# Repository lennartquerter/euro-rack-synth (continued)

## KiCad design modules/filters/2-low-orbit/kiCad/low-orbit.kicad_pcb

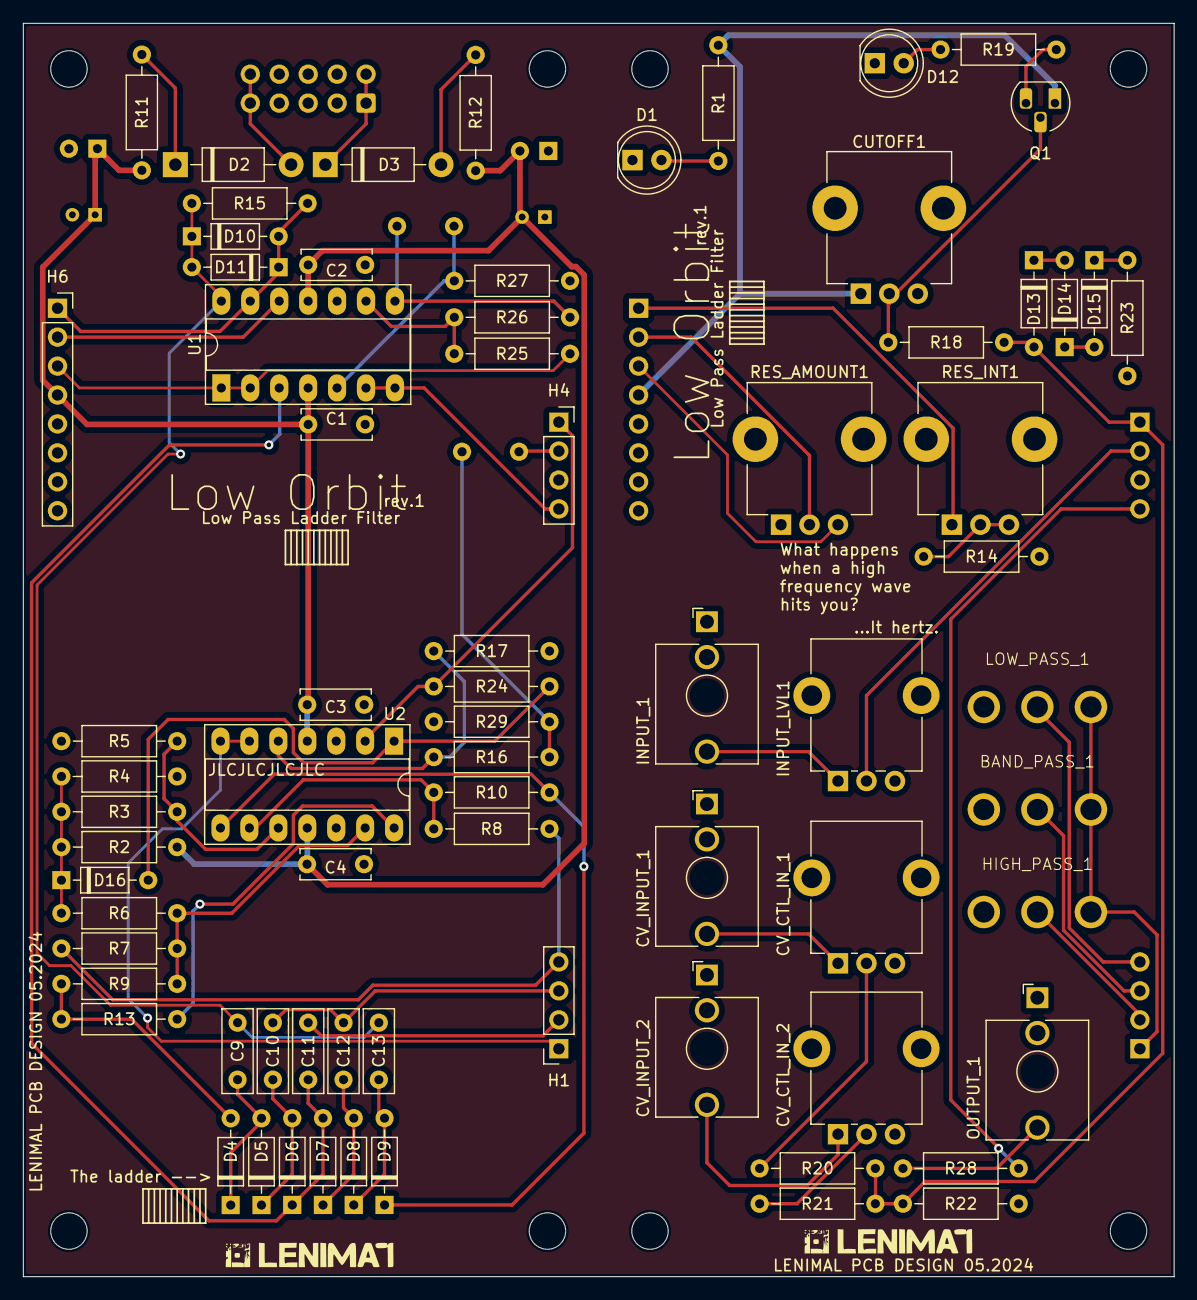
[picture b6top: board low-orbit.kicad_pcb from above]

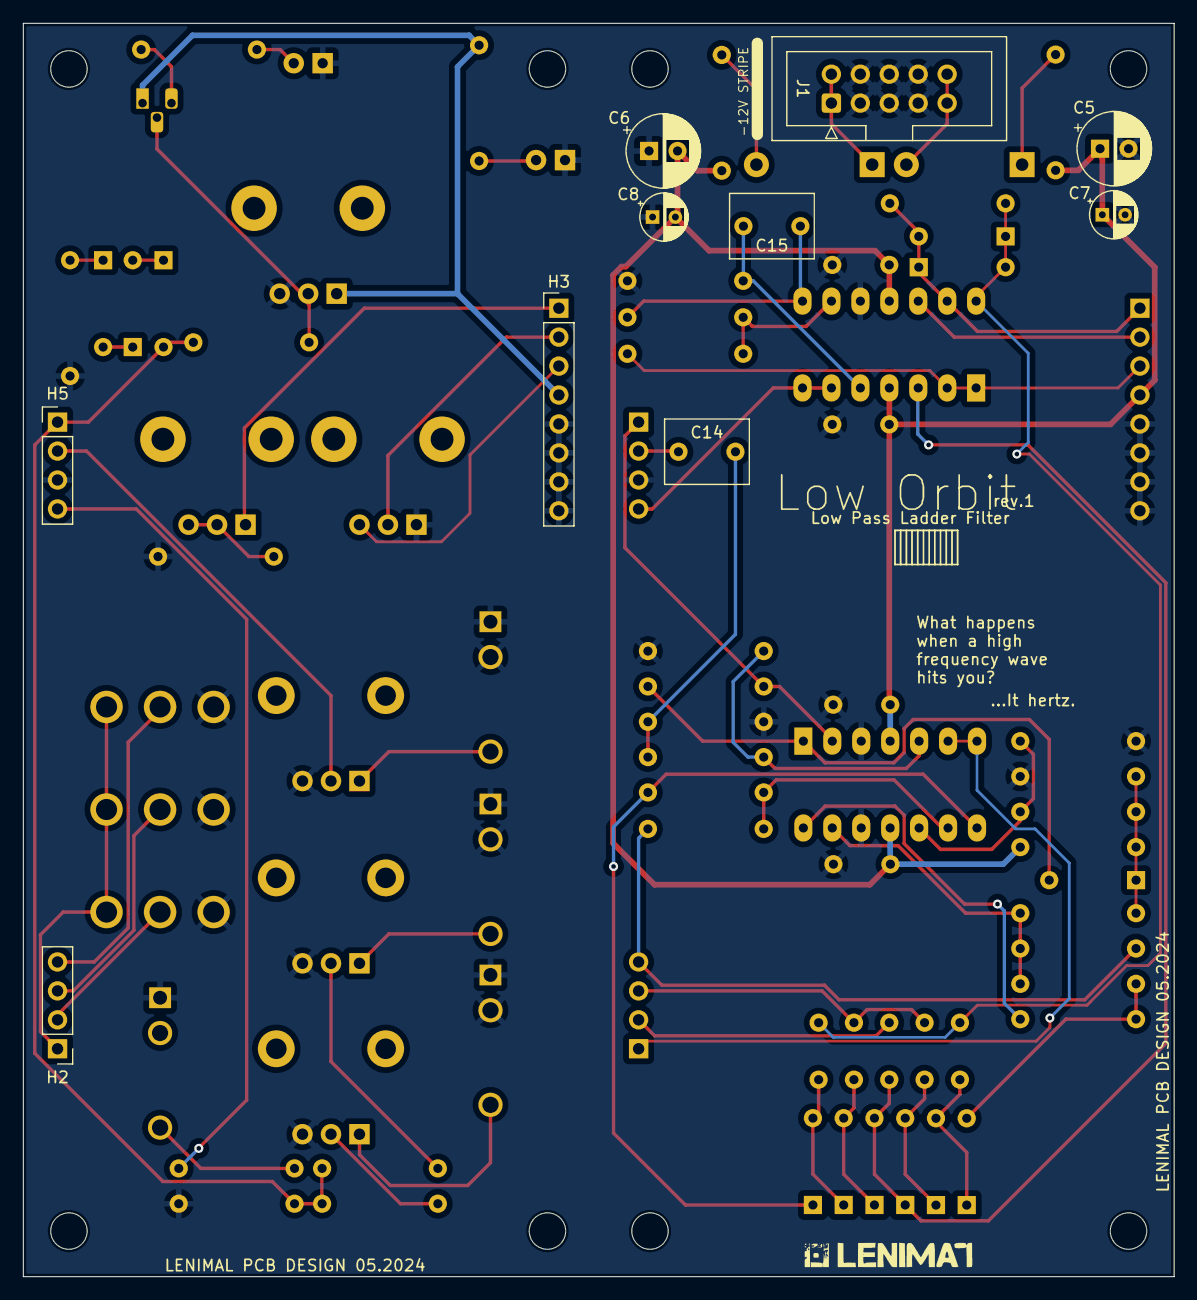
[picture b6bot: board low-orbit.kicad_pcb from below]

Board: 2 copper layers, 101.0 x 110.0 mm, 91 parts (10 on the bottom side), 60 nets.

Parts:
BAND_PASS_1: BAND_PASS; SW_default
C1, C2, C3, C4: 0.1uF; C_Disc_D6.0mm_W2.5mm_P5.00mm
C5, C6: 47uF; CP_Radial_D6.3mm_P2.50mm
C7, C8: 0.1uF; CP_Radial_D4.0mm_P2.00mm
C9, C10, C11, C12, C13: 1nF [2,5%]; C_RECT_WIMA_0.1uF
C14: 1uF; C_RECT_MKT_1uF
C15: C_1uF (MKS); C_RECT_MKT_1uF
CUTOFF1: B100K; Potentiometer_TT_P0915N
CV_CTL_IN_1, CV_CTL_IN_2: B100K; Potentiometer_Alpha_RD901F-40-00D_Single_Vertical_CircularH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
CV_INPUT_1: CV_INPUT_1; Jack_3.5mm_QingPu_WQP-PJ398SM_Vertical_CircularHoles
CV_INPUT_2: CV_INPUT_2; Jack_3.5mm_QingPu_WQP-PJ398SM_Vertical_CircularHoles
D1, D12: LED; LED_D5.0mm (center Aligned)
D2, D3: 1N5819; D_DO-41_SOD81_P10.16mm_Horizontal
D4, D5, D6, D7, D8, D9, D10, D11, D13, D14, D15, D16: 1N4148; D_DO-35_SOD27_P7.62mm_Horizontal
H1, H4: PinSocket_01x04; PinSocket_1x04_P2.54mm_Vertical
H2, H5: PinHeader_01x04; PinHeader_1x04_P2.54mm_Vertical
H3: PinHeader_01x08; PinHeader_1x08_P2.54mm_Vertical
H6: PinSocket_01x08; PinSocket_1x08_P2.54mm_Vertical
H7, H8, H9, H10, H11, H12, H13, H14: MountingHole; MountingHole_3.2mm_M3
HIGH_PASS_1: HIGH_PASS; SW_default
INPUT_1: IN; Jack_3.5mm_QingPu_WQP-PJ398SM_Vertical_CircularHoles
INPUT_LVL1: B100K; Potentiometer_Alpha_RD901F-40-00D_Single_Vertical_CircularH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
J1: PWR; IDC-Header_2x05_P2.54mm_Vertical
LOW_PASS_1: LOW_PASS; SW_default
OUTPUT_1: FILTER_OUT; Jack_3.5mm_QingPu_WQP-PJ398SM_Vertical_CircularHoles
Q1: BC548; TO-92_HandSolder
R1, R19: 470R; R_Default (DIN0207)
R2, R15, R18, R27, R29: 100K; R_Default (DIN0207)
R3, R5, R6, R7, R8, R9, R10: 33K [1%]; R_Default (DIN0207)
R4: 27K; R_Default (DIN0207)
R11, R12: 10R; R_Default (DIN0207)
R13: 2K; R_Default (DIN0207)
R14, R23, R25, R28: 1K; R_Default (DIN0207)
R16, R26: 33K; R_Default (DIN0207)
R17: 680R; R_Default (DIN0207)
R20, R21, R22: 47K [1%]; R_Default (DIN0207)
R24: 14K; R_Default (DIN0207)
RES_AMOUNT1: B100K; Potentiometer_TT_P0915N
RES_INT1: B50K; Potentiometer_TT_P0915N
U1, U2: TL074; DIP-14_W7.62mm_Socket_LongPads

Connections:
+12V: C1.1, C3.1, C5.1, C7.1, CUTOFF1.1, H3.4, H6.4, Q1.1 (C), R1.1, R11.1, U1.4 (V+), U2.4 (V+)
-12V: C2.2, C4.2, C6.2, C8.2, R2.2, R12.1, U1.11 (V-), U2.11 (V-)
/cv-input/cv_out: D16.1 (K), R2.1, R3.2, R4.2, R6.1
/input/output: H1.1, U2.6 (-), U2.7
/output/input: H6.3, R25.1, U1.1, U1.2 (-)
/resonance/input: H3.3, RES_AMOUNT1.3
/resonance/output: C9.1, C13.1, D10.1 (K), D11.2 (A), R15.1, U1.14
GNDREF: BAND_PASS_1.1 (A), C1.2, C2.1, C3.2, C4.1, C5.2, C6.1, C7.2, C8.1, CUTOFF1.3, CV_CTL_IN_1.3, CV_CTL_IN_2.3, CV_INPUT_1.S, CV_INPUT_1.TN, CV_INPUT_2.S, CV_INPUT_2.TN, D1.1 (K), D12.1 (K), H3.5, H3.6, H3.7, H3.8, H4.3, H5.3, H6.5, H6.6, H6.7, H6.8, HIGH_PASS_1.1 (A), INPUT_1.S, INPUT_1.TN, INPUT_LVL1.3, J1.3, J1.4, J1.5, J1.6, J1.7, J1.8, LOW_PASS_1.1 (A), OUTPUT_1.S, R4.1, R5.1, R14.2, R17.1, R22.2, R23.2, R27.1, R29.2, RES_AMOUNT1.1, U1.10 (+), U2.3 (+), U2.12 (+)
unnamed: BAND_PASS_1.2 (B), H2.3
unnamed: BAND_PASS_1.3 (C), H2.1, HIGH_PASS_1.3 (C), LOW_PASS_1.3 (C)
unnamed: C14.2, R16.2, R29.1
unnamed: C15.1, R26.2, U1.8
unnamed: CV_CTL_IN_1.1, CV_INPUT_1.T
unnamed: CV_CTL_IN_1.2, R20.2
unnamed: CV_CTL_IN_2.1, CV_INPUT_2.T
unnamed: CV_CTL_IN_2.2, R21.2
unnamed: D1.2 (A), R1.2
unnamed: D2.2 (A), J1.9, J1.10
unnamed: D2.1 (K), R11.2
unnamed: D3.2 (A), R12.2
unnamed: D3.1 (K), J1.1, J1.2
unnamed: D4.2 (A), R9.2, R13.2
unnamed: C9.2, D4.1 (K), D5.2 (A)
unnamed: C10.2, D5.1 (K), D6.2 (A)
unnamed: C11.2, D6.1 (K), D7.2 (A), U1.3 (+)
unnamed: C12.2, D7.1 (K), D8.2 (A)
unnamed: C13.2, D8.1 (K), D9.2 (A)
unnamed: D9.1 (K), R10.1, U2.8
unnamed: D10.2 (A), D11.1 (K), H6.1 (Pin_3), R15.2, U1.13 (-)
unnamed: D12.2 (A), R19.2
unnamed: D13.2 (A), H5.1, R18.1, R20.1, R21.1, R22.1
unnamed: D13.1 (K), D14.2 (A)
unnamed: D14.1 (K), D15.2 (A)
unnamed: D15.1 (K), R23.1
unnamed: D16.2 (A), R24.1, U2.1
unnamed: C11.1, H1.2
unnamed: C10.1, C12.1, H1.3
unnamed: H1.4, R7.1, R8.1
unnamed: H2.2, HIGH_PASS_1.2 (B)
unnamed: H2.4, LOW_PASS_1.2 (B)
unnamed: H3.1, RES_INT1.1
unnamed: H3.2, RES_AMOUNT1.2
unnamed: H4.1, R24.2, U2.2 (-)
unnamed: C14.1, H4.2
unnamed: H4.4, U1.6 (-), U1.7
unnamed: H5.2, INPUT_LVL1.2
unnamed: H5.4, R28.2
unnamed: H6.2, U1.12 (+)
unnamed: INPUT_1.T, INPUT_LVL1.1
unnamed: OUTPUT_1.T, R28.1
unnamed: CUTOFF1.2, Q1.2 (B), R18.2
unnamed: Q1.3 (E), R19.1
unnamed: R13.1, U2.14
unnamed: R14.1, RES_INT1.2, RES_INT1.3
unnamed: C15.2, R27.2, U1.5 (+)
unnamed: R25.2, R26.1, U1.9 (-)
unnamed: R16.1, R17.2, U2.5 (+)
unnamed: R3.1, R5.2, U2.10 (+)
unnamed: R8.2, R10.2, U2.9 (-)
unnamed: R6.2, R7.2, R9.1, U2.13 (-)

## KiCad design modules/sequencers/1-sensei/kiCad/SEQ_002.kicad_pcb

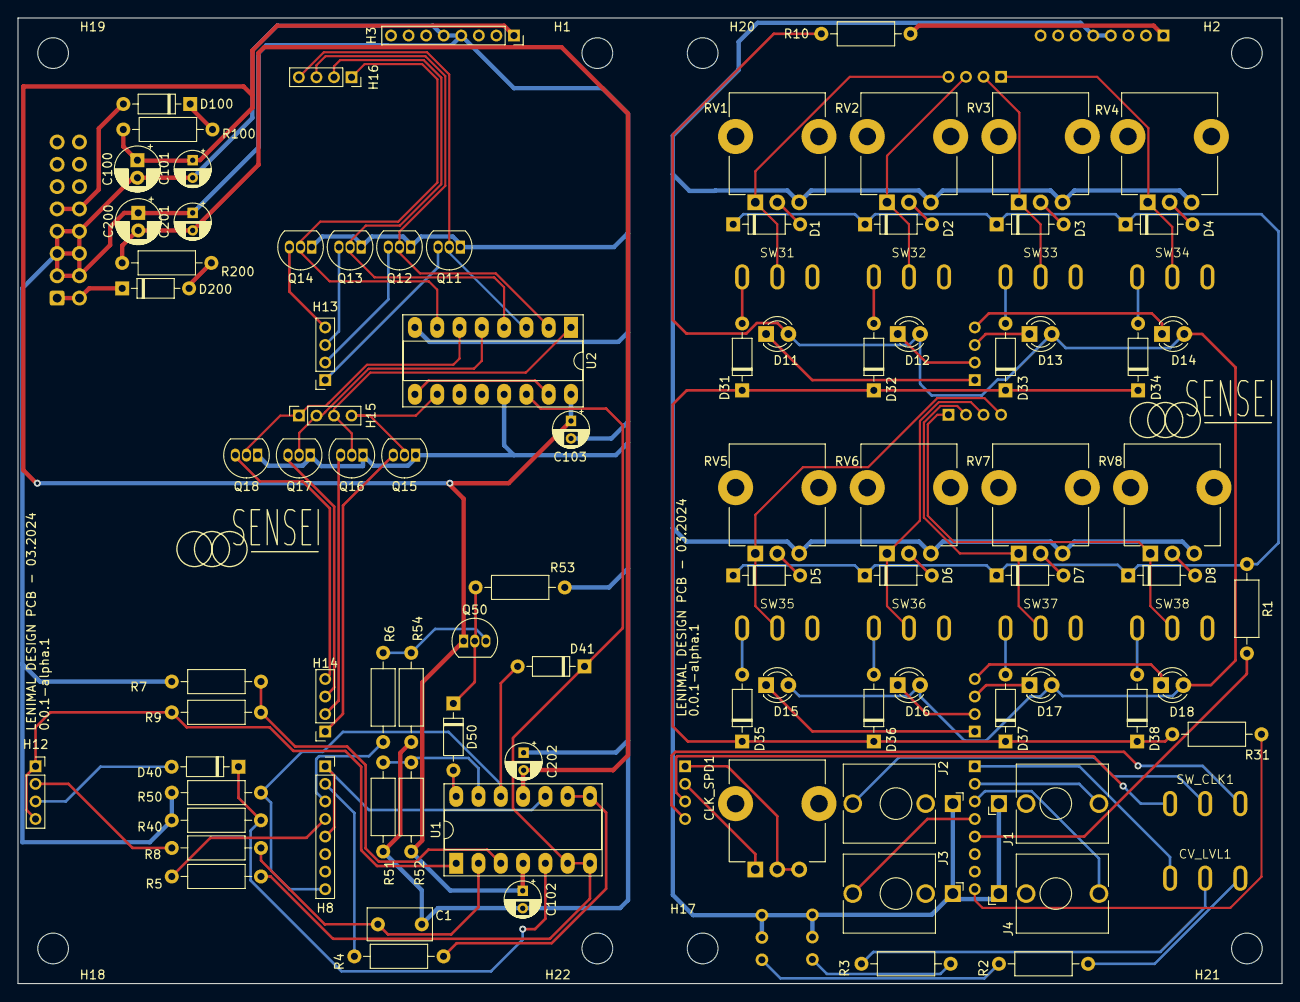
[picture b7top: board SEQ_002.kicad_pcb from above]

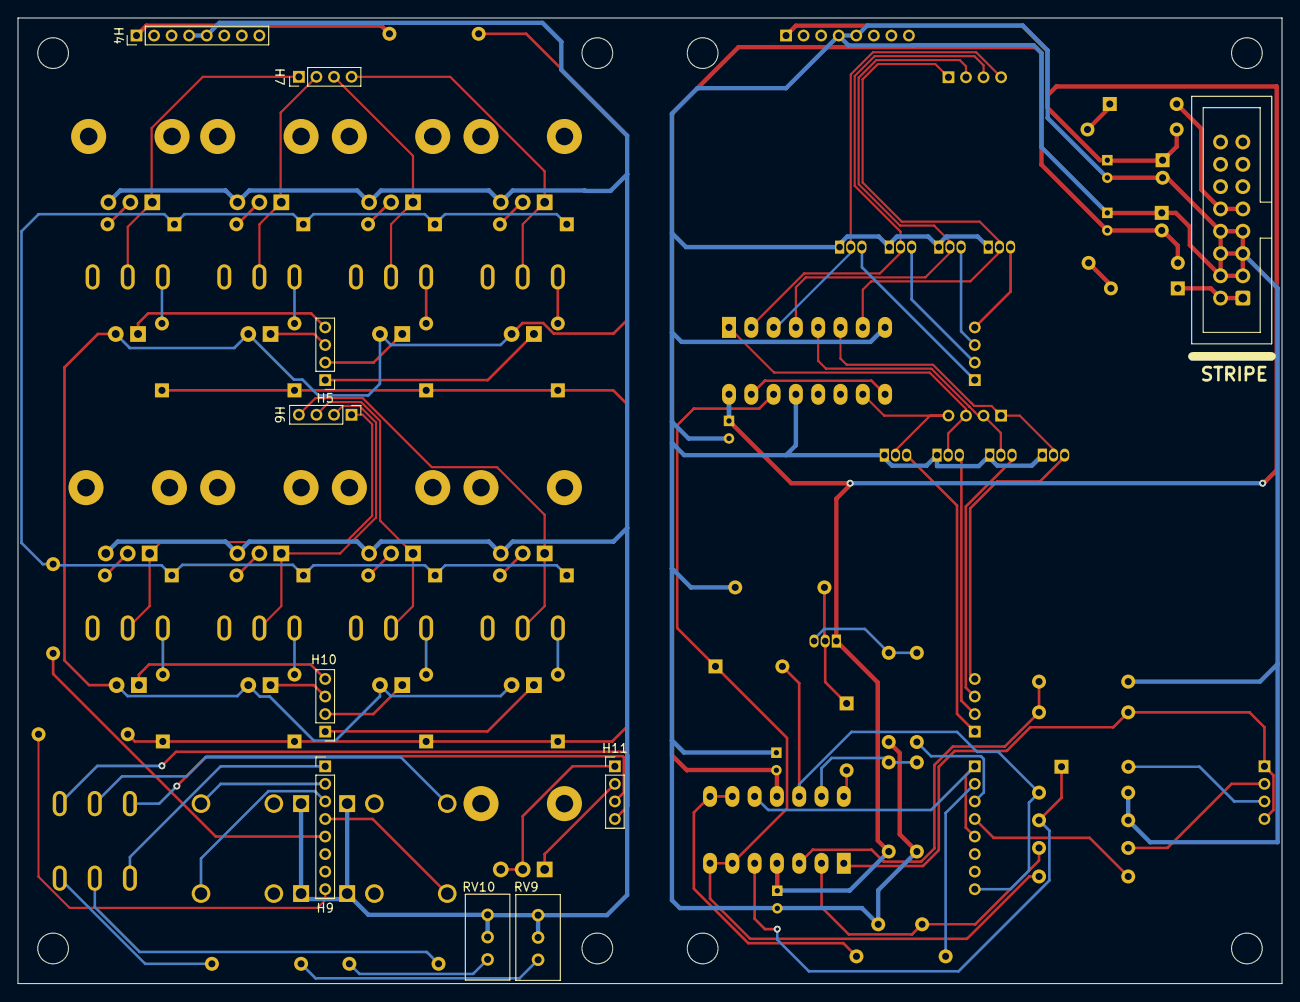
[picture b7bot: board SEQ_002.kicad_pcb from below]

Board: 2 copper layers, 144.0 x 110.0 mm, 115 parts (10 on the bottom side), 91 nets.

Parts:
C1: 0.1 uF; C_Rect_L7.2mm_W3.5mm_P5.00mm_FKS2_FKP2_MKS2_MKP2
C100, C200: 47uF; CP_Radial_D5.0mm_P2.00mm
C101, C102, C103, C201, C202: 0.1uF; CP_Radial_D4.0mm_P2.00mm
CLK_SPD1: B250K; Potentiometer_TT_P0915N
CV_LVL1: SPDT_Toggle
D1, D2, D3, D4, D5, D6, D7, D8, D31, D32, D33, D34, D35, D36, D37, D38, D40, D41, D50: 1N4148; D_DO-35_SOD27_P7.62mm_Horizontal
D11, D12, D13, D14, D15, D16, D17, D18: LED; LED_D3.0mm
D100, D200: 1N5819; D_DO-35_SOD27_P7.62mm_Horizontal
H1, H2, H17, H18, H19, H20, H21, H22: MountingHole; MountingHole_3.5mm
H3: BTM_PWR; PinSocket_1x08_P2.00mm_Vertical
H4: TOP_PWR; PinHeader_1x08_P2.00mm_Vertical
H5: TOP_LED_RW_1; PinHeader_1x04_P2.00mm_Vertical
H6: TOP_SGL_RW_1; PinHeader_1x04_P2.00mm_Vertical
H7: TOP_SGL_RW_2; PinHeader_1x04_P2.00mm_Vertical
H8: BTM_CTRL; PinSocket_1x08_P2.00mm_Vertical
H9: TOP_CTRL; PinHeader_1x08_P2.00mm_Vertical
H10: TOP_LED_RW_2; PinHeader_1x04_P2.00mm_Vertical
H11: TOP_CLK; PinHeader_1x04_P2.00mm_Vertical
H12: BTM_CLK; PinSocket_1x04_P2.00mm_Vertical
H13: BTM_LED_RW_1; PinSocket_1x04_P2.00mm_Vertical
H14: BTM_LED_RW_2; PinSocket_1x04_P2.00mm_Vertical
H15: BTM_SGL_RW_1; PinSocket_1x04_P2.00mm_Vertical
H16: BTM_SGL_RW_2; PinSocket_1x04_P2.00mm_Vertical
J1: CV OUT; Jack_3.5mm_QingPu_WQP-PJ398SM_Vertical_CircularHoles
J2: CLK_IN; Jack_3.5mm_QingPu_WQP-PJ398SM_Vertical_CircularHoles
J3: CLK OUT; Jack_3.5mm_QingPu_WQP-PJ398SM_Vertical_CircularHoles
J4: GATE OUT; Jack_3.5mm_QingPu_WQP-PJ398SM_Vertical_CircularHoles
J100: PWR; CONN_02x08_PWR
Q11, Q12, Q13, Q14, Q15, Q16, Q17, Q18: 2N3904; TO-92_Inline
Q50: BC547; TO-92_Inline
R1: 68K; R_Axial_DIN0207_L6.3mm_D2.5mm_P10.16mm_Horizontal
R2: 51K; R_Axial_DIN0207_L6.3mm_D2.5mm_P10.16mm_Horizontal
R3: 18K; R_Axial_DIN0207_L6.3mm_D2.5mm_P10.16mm_Horizontal
R4, R5, R10: 1K; R_Axial_DIN0207_L6.3mm_D2.5mm_P10.16mm_Horizontal
R6: 200; R_Axial_DIN0207_L6.3mm_D2.5mm_P10.16mm_Horizontal
R7, R9, R31, R40, R50, R52, R53: 100K; R_Axial_DIN0207_L6.3mm_D2.5mm_P10.16mm_Horizontal
R8: 2K; R_Axial_DIN0207_L6.3mm_D2.5mm_P10.16mm_Horizontal
R51: 47K; R_Axial_DIN0207_L6.3mm_D2.5mm_P10.16mm_Horizontal
R54: 4K7; R_Axial_DIN0207_L6.3mm_D2.5mm_P10.16mm_Horizontal
R100, R200: 10; R_Axial_DIN0207_L6.3mm_D2.5mm_P10.16mm_Horizontal
RV1, RV2, RV3, RV4, RV5, RV6, RV7, RV8: B100K; Potentiometer_TT_P0915N
RV9: 5K; Potentiometer_Bourns_3296W_Vertical
RV10: 2K; Potentiometer_Bourns_3296W_Vertical
SW31, SW32, SW33, SW34, SW35, SW36, SW37, SW38: SPDT_Toggle
SW_CLK1: SPDT_Toggle
U1: TL074; DIP-14_W7.62mm_Socket_LongPads
U2: 4017; DIP-16_W7.62mm_Socket_LongPads

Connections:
+12V: C100.1, C101.1, C102.1, C103.1, H3.1, H4.1, Q50.1 (C), R10.1, R52.1, R100.1, U1.4 (V+), U2.16 (VDD)
-12V: C200.2, C201.2, C202.2, R200.1, U1.11 (V-)
/TOGGLE/SW_DRIVER_1: H7.4, RV1.1, SW31.1 (A)
/TOGGLE/SW_DRIVER_2: H7.3, RV2.1, SW32.1 (A)
/TOGGLE/SW_DRIVER_3: H7.2, RV3.1, SW33.1 (A)
/TOGGLE/SW_DRIVER_4: H7.1, RV4.1, SW34.1 (A)
/TOGGLE/SW_DRIVER_5: H6.4, RV5.1, SW35.1 (A)
/TOGGLE/SW_DRIVER_6: H6.3, RV6.1, SW36.1 (A)
/TOGGLE/SW_DRIVER_7: H6.2, RV7.1, SW37.1 (A)
/TOGGLE/SW_DRIVER_8: H6.1, RV8.1, SW38.1 (A)
/TOGGLE/SW_OUT: H9.8, R31.2
/led_drivers/LED_DRIVER_1: H16.4, Q11.2 (B), U2.3 (Q0)
/led_drivers/LED_DRIVER_2: H16.3, Q12.2 (B), U2.2 (Q1)
/led_drivers/LED_DRIVER_3: H16.2, Q13.2 (B), U2.4 (Q2)
/led_drivers/LED_DRIVER_4: H16.1, Q14.2 (B), U2.7 (Q3)
/led_drivers/LED_DRIVER_5: H15.4, Q15.2 (B), U2.10 (Q4)
/led_drivers/LED_DRIVER_6: H15.3, Q16.2 (B), U2.1 (Q5)
/led_drivers/LED_DRIVER_7: H15.2, Q17.2 (B), U2.5 (Q6)
/led_drivers/LED_DRIVER_8: H15.1, Q18.2 (B), U2.6 (Q7)
GNDD: C1.1, C100.2, C101.2, C102.2, C103.2, C200.1, C201.1, C202.1, H3.4, H3.5, H4.4, H4.5, J1.S, J2.S, J3.S, J4.S, J100.3 (GND), J100.4 (GND), J100.5 (GND), J100.6 (GND), J100.7 (GND), J100.8 (GND), Q11.1 (E), Q12.1 (E), Q13.1 (E), Q14.1 (E), Q15.1 (E), Q16.1 (E), Q17.1 (E), Q18.1 (E), R7.2, R40.1, R50.1, R51.1, R53.1, R54.1, RV1.3, RV2.3, RV3.3, RV4.3, RV5.3, RV6.3, RV7.3, RV8.3, RV9.2, RV9.3, RV10.2, RV10.3, U2.8 (VSS), U2.13 (CKEN)
unnamed: CLK_SPD1.1, H11.2
unnamed: CLK_SPD1.2, CLK_SPD1.3, H11.1
unnamed: CV_LVL1.1 (A), R3.2
unnamed: CV_LVL1.2 (B), H9.1
unnamed: CV_LVL1.3 (C), R2.2
unnamed: D1.2 (A), RV1.2
unnamed: D1.1 (K), D2.1 (K), D3.1 (K), D4.1 (K), D5.1 (K), D6.1 (K), D7.1 (K), D8.1 (K), R1.1
unnamed: D2.2 (A), RV2.2
unnamed: D3.2 (A), RV3.2
unnamed: D4.2 (A), RV4.2
unnamed: D5.2 (A), RV5.2
unnamed: D6.2 (A), RV6.2
unnamed: D7.2 (A), RV7.2
unnamed: D8.2 (A), RV8.2
unnamed: D11.2 (A), D12.2 (A), D13.2 (A), D14.2 (A), D15.2 (A), D16.2 (A), D17.2 (A), D18.2 (A), R10.2
unnamed: D11.1 (K), H5.1
unnamed: D12.1 (K), H5.2
unnamed: D13.1 (K), H5.3
unnamed: D14.1 (K), H5.4
unnamed: D15.1 (K), H10.1
unnamed: D16.1 (K), H10.2
unnamed: D17.1 (K), H10.3
unnamed: D18.1 (K), H10.4
unnamed: D31.2 (A), SW31.2 (B)
unnamed: D31.1 (K), D32.1 (K), D33.1 (K), D34.1 (K), D35.1 (K), D36.1 (K), D37.1 (K), D38.1 (K), R31.1
unnamed: D32.2 (A), SW32.2 (B)
unnamed: D33.2 (A), SW33.2 (B)
unnamed: D34.2 (A), SW34.2 (B)
unnamed: D35.2 (A), SW35.2 (B)
unnamed: D36.2 (A), SW36.2 (B)
unnamed: D37.2 (A), SW37.2 (B)
unnamed: D38.2 (A), SW38.2 (B)
unnamed: D40.2 (A), H12.3
unnamed: D40.1 (K), R40.2, U1.5 (+)
unnamed: D41.2 (A), H8.8, R50.2, U1.12 (+)
unnamed: D41.1 (K), R5.2, U1.6 (-), U1.7, U2.14 (CLK)
unnamed: D50.2 (A), U1.14
unnamed: D50.1 (K), Q50.2 (B), R53.2
unnamed: D100.2 (A), J100.9 (+12V), J100.10 (+12V)
unnamed: D100.1 (K), R100.2
unnamed: D200.2 (A), R200.2
unnamed: D200.1 (K), J100.1 (-12V), J100.2 (-12V)
unnamed: H8.2, R4.1
unnamed: H8.3, R6.1
unnamed: H8.4, R5.1
unnamed: H9.2, J1.T
unnamed: H9.3, J4.T
unnamed: H9.4, J3.T
unnamed: H9.5, R1.2
unnamed: H12.1, H12.4, R9.1, U1.1
unnamed: H12.2, R8.1
unnamed: H13.1, Q11.3 (C)
unnamed: H13.2, Q12.3 (C)
unnamed: H13.3, Q13.3 (C)
unnamed: H13.4, Q14.3 (C)
unnamed: H14.1, Q15.3 (C)
unnamed: H14.2, Q16.3 (C)
unnamed: H14.3, Q17.3 (C)
unnamed: H14.4, Q18.3 (C)
unnamed: Q50.3 (E), R6.2, R54.2
unnamed: R2.1, RV9.1
unnamed: R3.1, RV10.1
unnamed: J2.T, SW_CLK1.1 (A)
unnamed: H11.3, SW_CLK1.2 (B)
unnamed: H11.4, SW_CLK1.3 (C)
unnamed: R7.1, R9.2, U1.3 (+)
unnamed: C1.2, R8.2, U1.2 (-)
unnamed: H8.1, H8.5, U1.10 (+)
unnamed: R4.2, U1.8, U1.9 (-)
unnamed: R51.2, R52.2, U1.13 (-)
unnamed: U2.9 (Q8), U2.15 (Reset)

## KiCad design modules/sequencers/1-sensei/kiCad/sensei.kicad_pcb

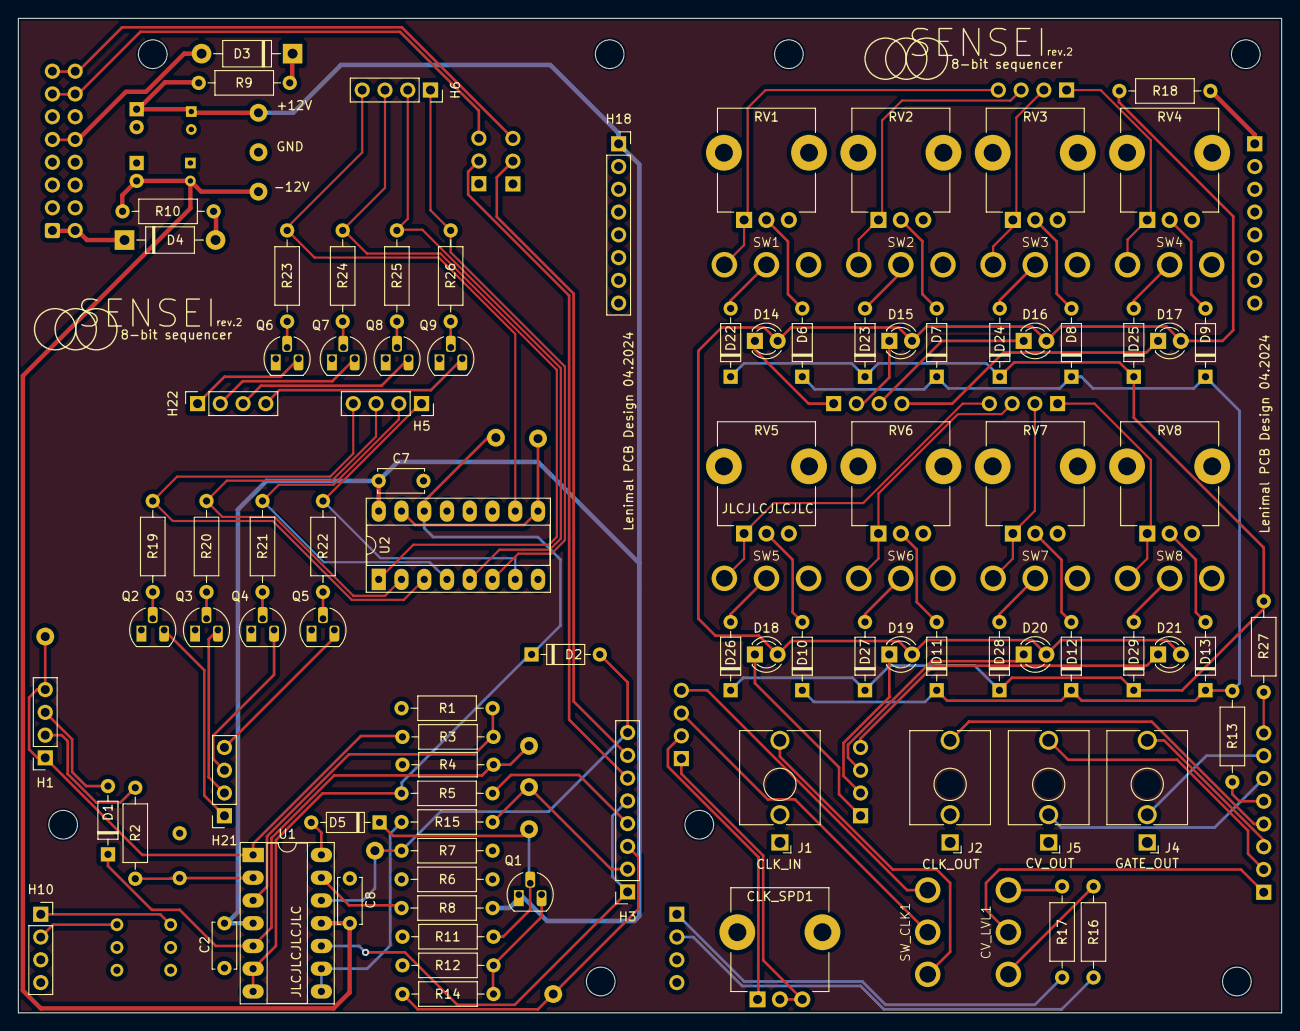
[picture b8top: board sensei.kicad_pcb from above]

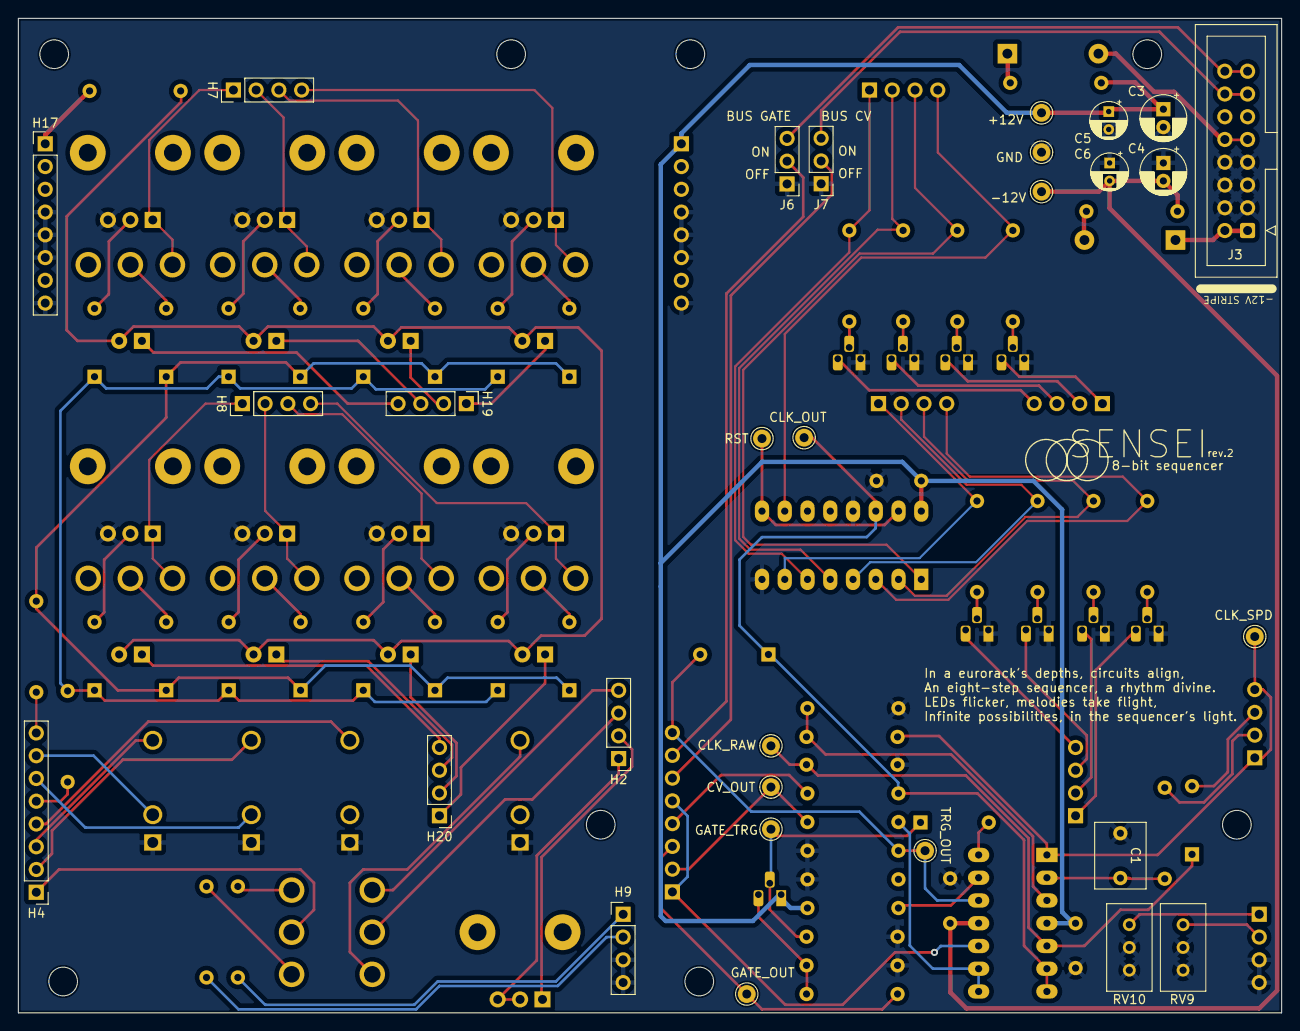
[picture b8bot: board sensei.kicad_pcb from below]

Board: 2 copper layers, 141.0 x 111.0 mm, 138 parts (29 on the bottom side), 107 nets.

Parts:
C1: 1uF; C_RECT_MKT_1uF
C2, C7, C8: 0.1uF; C_Disc_D5.0mm_W2.5mm_P5.00mm
C3, C4: 47uF; CP_Radial_D5.0mm_P2.00mm
C5, C6: 0.1uF; CP_Radial_D4.0mm_P2.00mm
CLK_SPD1: B250K; Potentiometer_TT_P0915N
CV_LVL1: SW_default
D1, D2, D5, D6, D7, D8, D9, D10, D11, D12, D13, D22, D23, D24, D25, D26, D27, D28, D29: 1N4148; D_DO-35_SOD27_P7.62mm_Horizontal
D3, D4: 1N5819; D_DO-41_SOD81_P10.16mm_Horizontal
D14, D15, D16, D17, D18, D19, D20, D21: LED; LED_D3.0mm
H1, H5, H6, H10, H21, H22: PinSocket_1x04; PinSocket_1x04_P2.54mm_Vertical
H2, H7, H8, H9, H19, H20: PinHeader_1x04; PinHeader_1x04_P2.54mm_Vertical
H3, H18: PinSocket_1x08; PinSocket_1x08_P2.54mm_Vertical
H4, H17: PinHeader_1x08; PinHeader_1x08_P2.54mm_Vertical
J1: CLK_IN; Jack_3.5mm_QingPu_WQP-PJ398SM_Vertical_CircularHoles
J2: CLK OUT; Jack_3.5mm_QingPu_WQP-PJ398SM_Vertical_CircularHoles
J3: PWR; IDC-Header_2x08_P2.54mm_Vertical
J4: GATE OUT; Jack_3.5mm_QingPu_WQP-PJ398SM_Vertical_CircularHoles
J5: CV OUT; Jack_3.5mm_QingPu_WQP-PJ398SM_Vertical_CircularHoles
J6, J7: PinHeader_1x03; PinHeader_1x03_P2.54mm_Vertical
M1, M2, M3, M4, M5, M6, M7, M8: MountingHole; MountingHole_3.2mm_M3
Q1: BC547; TO-92_HandSolder
Q2, Q3, Q4, Q5, Q6, Q7, Q8, Q9: 2N3904; TO-92_HandSolder
R1, R3, R4, R7, R8, R11, R19, R20, R21, R22, R23, R24, R25, R26, R27: 100K; R_Default (DIN0207)
R2: 2K; R_Default (DIN0207)
R5, R15: 1K; R_Default (DIN0207)
R6: 47K; R_Default (DIN0207)
R9, R10: 10R; R_Default (DIN0207)
R12: 4K7; R_Default (DIN0207)
R13: 68K; R_Default (DIN0207)
R14: 200R; R_Default (DIN0207)
R16: 18K; R_Default (DIN0207)
R17: 51K; R_Default (DIN0207)
R18: 470R; R_Default (DIN0207)
RV1, RV2, RV3, RV4, RV5, RV6, RV7, RV8: B100K; Potentiometer_TT_P0915N
RV9: 2K; Potentiometer_Bourns_3296W_Vertical
RV10: 5K; Potentiometer_Bourns_3296W_Vertical
SW1, SW2, SW3, SW4, SW5, SW6, SW7, SW8: SW_default
SW_CLK1: SW_default
TP1, TP2, TP3, TP4, TP5, TP6, TP7, TP8, TP9, TP10, TP11: TestPoint; Pin_D1.0mm_L10.0mm
U1: TL074; DIP-14_W7.62mm_Socket_LongPads
U2: CD4017; DIP-16_W7.62mm_Socket_LongPads

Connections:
+12V: C2.1, C3.1, C5.1, C7.1, H17.1, H18.1 (Pin_3), Q1.1 (C), R8.2, R9.2, R18.2, TP9.1, U1.4 (V+), U2.16 (VDD)
-12V: C4.2, C6.2, C8.2, R10.2, TP11.1, U1.11 (V-)
/TOGGLE/SW_DRIVER_1: H7.4, RV1.1, SW1.1 (A)
/TOGGLE/SW_DRIVER_2: H7.3, RV2.1, SW2.1 (A)
/TOGGLE/SW_DRIVER_3: H7.2, RV3.1, SW3.1 (A)
/TOGGLE/SW_DRIVER_4: H7.1, RV4.1, SW4.1 (A)
/TOGGLE/SW_DRIVER_5: H8.4, RV5.1, SW5.1 (A)
/TOGGLE/SW_DRIVER_6: H8.3, RV6.1, SW6.1 (A)
/TOGGLE/SW_DRIVER_7: H8.2, RV7.1, SW7.1 (A)
/TOGGLE/SW_DRIVER_8: H8.1, RV8.1, SW8.1 (A)
/TOGGLE/SW_OUT: H4.8, R27.1
/led_drivers/LED_DRIVER_1: H5.4, R19.2, U2.3 (Q0)
/led_drivers/LED_DRIVER_2: H5.3, R20.2, U2.2 (Q1)
/led_drivers/LED_DRIVER_3: H5.2, R21.2, U2.4 (Q2)
/led_drivers/LED_DRIVER_4: H5.1, R22.2, U2.7 (Q3)
/led_drivers/LED_DRIVER_5: H6.4, R23.2, U2.10 (Q4)
/led_drivers/LED_DRIVER_6: H6.3, R24.2, U2.1 (Q5)
/led_drivers/LED_DRIVER_7: H6.2, R25.2, U2.5 (Q6)
/led_drivers/LED_DRIVER_8: H6.1, R26.2, U2.6 (Q7)
GNDREF: C1.1, C2.2, C3.2, C4.1, C5.2, C6.1, C7.2, C8.1, H9.3, H9.4, H10.3, H10.4, H17.4, H17.5, H17.6, H17.8, H18.4, H18.5, H18.6, H18.8, J1.S, J2.S, J3.3 (GND), J3.4 (GND), J3.5 (GND), J3.6 (GND), J3.7 (GND), J3.8 (GND), J4.S, J5.S, J6.1, J7.1, Q2.1 (E), Q3.1 (E), Q4.1 (E), Q5.1 (E), Q6.1 (E), Q7.1 (E), Q8.1 (E), Q9.1 (E), R1.1, R4.2, R6.2, R7.2, R11.2, R12.2, RV1.3, RV2.3, RV3.3, RV4.3, RV5.3, RV6.3, RV7.3, RV8.3, RV9.2, RV9.3, RV10.2, RV10.3, TP10.1, U2.8 (VSS), U2.13 (CKEN)
unnamed: CV_LVL1.1 (A), R16.1
unnamed: CV_LVL1.2 (B), H4.1
unnamed: CV_LVL1.3 (C), R17.1
unnamed: D1.2 (A), H1.3
unnamed: D1.1 (K), R4.1, TP7.1, U1.5 (+)
unnamed: D2.2 (A), H3.8, R7.1, TP4.1, U1.12 (+)
unnamed: D2.1 (K), R5.1, TP3.1, U1.6 (-), U1.7, U2.14 (CLK)
unnamed: D3.2 (A), J3.9 (+12V), J3.10 (+12V)
unnamed: D3.1 (K), R9.1
unnamed: D4.2 (A), R10.1
unnamed: D4.1 (K), J3.1 (-12V), J3.2 (-12V)
unnamed: D5.2 (A), U1.14
unnamed: D5.1 (K), Q1.2 (B), R11.1, TP6.1
unnamed: D6.2 (A), RV1.2
unnamed: D7.2 (A), RV2.2
unnamed: D8.2 (A), RV3.2
unnamed: D9.2 (A), RV4.2
unnamed: D10.2 (A), RV5.2
unnamed: D6.1 (K), D7.1 (K), D8.1 (K), D9.1 (K), D10.1 (K), D11.1 (K), D12.1 (K), D13.1 (K), R13.2
unnamed: D11.2 (A), RV6.2
unnamed: D12.2 (A), RV7.2
unnamed: D13.2 (A), RV8.2
unnamed: D14.2 (A), D15.2 (A), D16.2 (A), D17.2 (A), D18.2 (A), D19.2 (A), D20.2 (A), D21.2 (A), R18.1
unnamed: D14.1 (K), H19.1
unnamed: D15.1 (K), H19.2
unnamed: D16.1 (K), H19.3
unnamed: D17.1 (K), H19.4
unnamed: D18.1 (K), H20.1
unnamed: D19.1 (K), H20.2
unnamed: D20.1 (K), H20.3
unnamed: D21.1 (K), H20.4
unnamed: D22.2 (A), SW1.2 (B)
unnamed: D22.1 (K), D23.1 (K), D24.1 (K), D25.1 (K), D26.1 (K), D27.1 (K), D28.1 (K), D29.1 (K), R27.2
unnamed: D23.2 (A), SW2.2 (B)
unnamed: D24.2 (A), SW3.2 (B)
unnamed: D25.2 (A), SW4.2 (B)
unnamed: D26.2 (A), SW5.2 (B)
unnamed: D27.2 (A), SW6.2 (B)
unnamed: D28.2 (A), SW7.2 (B)
unnamed: D29.2 (A), SW8.2 (B)
unnamed: H1.1, H1.4, R3.2, TP8.1, U1.1
unnamed: H1.2, R2.2
unnamed: CLK_SPD1.2, CLK_SPD1.3, H2.1
unnamed: CLK_SPD1.1, H2.2
unnamed: H2.3, SW_CLK1.2 (B)
unnamed: H2.4, SW_CLK1.3 (C)
unnamed: H3.1 (Pin_3), H3.5, U1.10 (+)
unnamed: H3.2, R15.2, TP1.1
unnamed: H3.3, R14.2, TP2.1
unnamed: H3.4, R5.2
unnamed: H3.6, J7.2
unnamed: H3.7, J6.2
unnamed: H4.2, J5.T
unnamed: H4.3, J4.T
unnamed: H4.4, J2.T
unnamed: H4.5, R13.1
unnamed: H4.6, J5.TN
unnamed: H4.7, J4.TN
unnamed: H9.1, R17.2
unnamed: H9.2, R16.2
unnamed: H10.1, RV10.1
unnamed: H10.2, RV9.1
unnamed: H21.1, Q2.3 (C)
unnamed: H21.2, Q3.3 (C)
unnamed: H21.3, Q4.3 (C)
unnamed: H21.4, Q5.3 (C)
unnamed: H22.1, Q6.3 (C)
unnamed: H22.2, Q7.3 (C)
unnamed: H22.3, Q8.3 (C)
unnamed: H22.4, Q9.3 (C)
unnamed: J3.15 (GATE), J3.16 (GATE), J6.3
unnamed: J3.13 (CV), J3.14 (CV), J7.3
unnamed: Q1.3 (E), R12.1, R14.1
unnamed: Q2.2 (B), R19.1
unnamed: Q3.2 (B), R20.1
unnamed: Q4.2 (B), R21.1
unnamed: Q5.2 (B), R22.1
unnamed: Q6.2 (B), R23.1
unnamed: Q7.2 (B), R24.1
unnamed: Q8.2 (B), R25.1
unnamed: Q9.2 (B), R26.1
unnamed: J1.T, SW_CLK1.1 (A)
unnamed: R1.2, R3.1, U1.3 (+)
unnamed: C1.2, R2.1, U1.2 (-)
unnamed: R15.1, U1.8, U1.9 (-)
unnamed: R6.1, R8.1, U1.13 (-)
unnamed: TP5.1, U2.9 (Q8), U2.15 (Reset)

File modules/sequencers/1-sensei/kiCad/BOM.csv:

"Reference","Value","Datasheet","Footprint","Qty","DNP"
"C1","0.1 uF","~","Synth:C_RECT_MKT_1uF","1",""
"C2,C5,C6,C7,C8","0.1uF","~","Capacitor_THT:CP_Radial_D4.0mm_P2.00mm","5",""
"C3,C4","47uF","~","Capacitor_THT:CP_Radial_D5.0mm_P2.00mm","2",""
"CLK_SPD1","B250K","~","Synth:Potentiometer_TT_P0915N","1",""
"CV_LVL1,SW1,SW2,SW3,SW4,SW5,SW6,SW7,SW8,SW_CLK1","~","~","Synth:SW_default","10",""
"D1,D2,D5,D6,D7,D8,D9,D10,D11,D12,D13,D22,D23,D24,D25,D26,D27,D28,D29","1N4148","https://assets.nexperia.com/documents/data-sheet/1N4148_1N4448.pdf","Synth:D_DO-35_SOD27_P7.62mm_Horizontal","19",""
"D3,D4","1N5819","http://www.vishay.com/docs/88525/1n5817.pdf","Synth:D_DO-41_SOD81_P10.16mm_Horizontal","2",""
"D14,D15,D16,D17,D18,D19,D20,D21","LED","~","LED_THT:LED_D3.0mm","8",""
"H1","BTM_CLK","~","Synth:PinSocket_1x04_P2.54mm_Vertical","1",""
"H2","TOP_CLK","~","Synth:PinHeader_1x04_P2.54mm_Vertical","1",""
"H3","BTM_CTRL","~","Synth:PinSocket_1x08_P2.54mm_Vertical","1",""
"H4","TOP_CTRL","~","Synth:PinHeader_1x08_P2.54mm_Vertical","1",""
"H5","BTM_SGL_RW_2","~","Synth:PinSocket_1x04_P2.54mm_Vertical","1",""
"H6","BTM_SGL_RW_1","~","Synth:PinSocket_1x04_P2.54mm_Vertical","1",""
"H7","TOP_SGL_RW_2","~","Synth:PinHeader_1x04_P2.54mm_Vertical","1",""
"H8","TOP_SGL_RW_1","~","Synth:PinHeader_1x04_P2.54mm_Vertical","1",""
"H9,H10,H11,H12,H13,H14,H15,H16","MountingHole","~","MountingHole:MountingHole_3.2mm_M3","8",""
"H17","TOP_PWR","~","Synth:PinHeader_1x08_P2.54mm_Vertical","1",""
"H18","BTM_PWR","~","Synth:PinSocket_1x08_P2.54mm_Vertical","1",""
"H19","TOP_LED_RW_1","~","Synth:PinHeader_1x04_P2.54mm_Vertical","1",""
"H20","TOP_LED_RW_2","~","Synth:PinHeader_1x04_P2.54mm_Vertical","1",""
"H21","BTM_LED_RW_1","~","Synth:PinSocket_1x04_P2.54mm_Vertical","1",""
"H22","BTM_LED_RW_2","~","Synth:PinSocket_1x04_P2.54mm_Vertical","1",""
"J1","CLK_IN","~","Synth:Jack_3.5mm_QingPu_WQP-PJ398SM_Vertical_CircularHoles","1",""
"J2","CLK OUT","~","Synth:Jack_3.5mm_QingPu_WQP-PJ398SM_Vertical_CircularHoles","1",""
"J3","PWR","~","Synth:IDC-Header_2x08_P2.54mm_Vertical","1",""
"J4","GATE OUT","~","Synth:Jack_3.5mm_QingPu_WQP-PJ398SM_Vertical_CircularHoles","1",""
"J5","CV OUT","~","Synth:Jack_3.5mm_QingPu_WQP-PJ398SM_Vertical_CircularHoles","1",""
"J6","GATE_BUS_ENABLE","~","Connector_PinHeader_2.54mm:PinHeader_1x03_P2.54mm_Vertical","1",""
"J7","CV_BUS_ENABLE","~","Connector_PinHeader_2.54mm:PinHeader_1x03_P2.54mm_Vertical","1",""
"J8","CV_LVL_BTM","~","-- mixed values --","1",""
"J9","CV_LVL_TOP","~","-- mixed values --","1",""
"Q1","BC547","https://www.onsemi.com/pub/Collateral/BC550-D.pdf","Package_TO_SOT_THT:TO-92_HandSolder","1",""
"Q2,Q3,Q4,Q5,Q6,Q7,Q8,Q9","2N3904","https://www.onsemi.com/pub/Collateral/2N3903-D.PDF","Package_TO_SOT_THT:TO-92_HandSolder","8",""
"R1,R3,R4,R7,R8,R11,R19,R20,R21,R22,R23,R24,R25,R26,R27","100K","~","Synth:R_Default (DIN0207)","15",""
"R2,RV9","2K","~","-- mixed values --","2",""
"R5,R15,R18","1K","~","Synth:R_Default (DIN0207)","3",""
"R6","47K","~","Synth:R_Default (DIN0207)","1",""
"R9,R10","10","~","Synth:R_Default (DIN0207)","2",""
"R12","4K7","~","Synth:R_Default (DIN0207)","1",""
"R13","68K","~","Synth:R_Default (DIN0207)","1",""
"R14","200","~","Synth:R_Default (DIN0207)","1",""
"R16","18K","~","Synth:R_Default (DIN0207)","1",""
"R17","51K","~","Synth:R_Default (DIN0207)","1",""
"RV1,RV2,RV3,RV4,RV5,RV6,RV7,RV8","B100K","~","Synth:Potentiometer_TT_P0915N","8",""
"RV10","5K","~","Potentiometer_THT:Potentiometer_Bourns_3296W_Vertical","1",""
"TP1,TP2,TP3,TP4,TP5,TP6,TP7,TP8,TP9,TP10,TP11","TestPoint","~","Connector_Pin:Pin_D1.0mm_L10.0mm","11",""
"U1","TL074","http://www.ti.com/lit/ds/symlink/tl071.pdf","Package_DIP:DIP-14_W7.62mm_Socket_LongPads","1",""
"U2","4017","http://www.intersil.com/content/dam/Intersil/documents/cd40/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","Package_DIP:DIP-16_W7.62mm_Socket_LongPads","1",""
